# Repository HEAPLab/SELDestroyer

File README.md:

This README is a WIP.

# SEL Destroyer
This repository contains the hardware, firmware and software files of the
**SEL Destroyer** board, which is an electronic device to detect and destroy
the Single Event Latches (SELs) happening during SEE testing of electronic
components (radiation testing, laser-based testing, etc.).

The SEL destroyer can be also used as a normal voltage, current, or power monitoring device.

## Features
...

## Repository structure
- The `hardware` directory contains the KiCad files
  - See the hardware readme (WIP)
- The `firmware` directory contains the MPLAB X project (XC8 compiler) to program the PIC microcontroller
  - See the firmware readme (WIP)
- The `software` directory contains the host software (PC-side)
  - Check the software [README](software/README.md)

## License
MIT license, see the [LICENSE](LICENSE) file.

## Acknowledgments

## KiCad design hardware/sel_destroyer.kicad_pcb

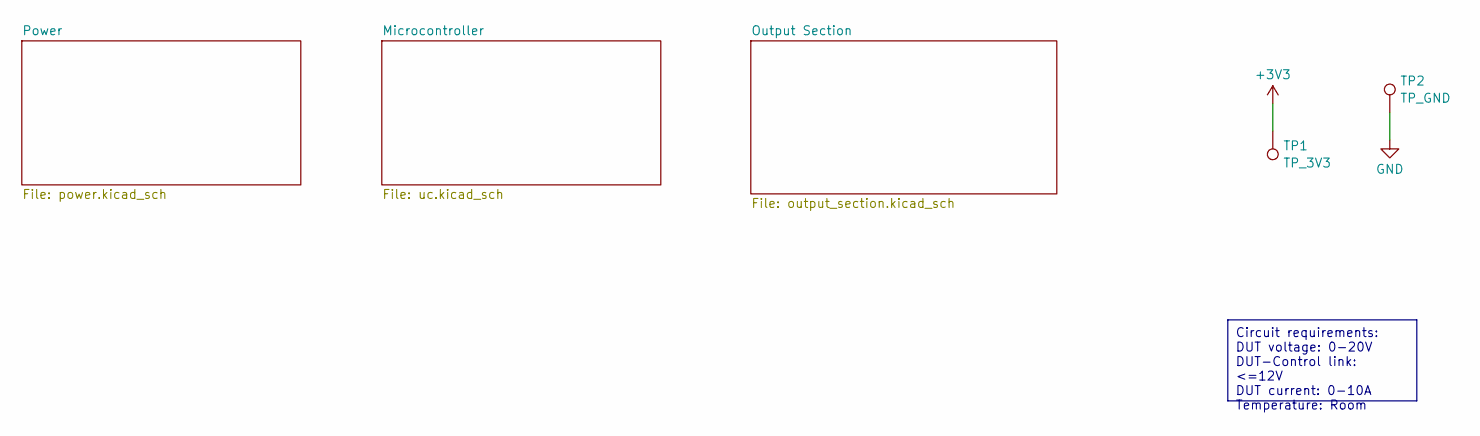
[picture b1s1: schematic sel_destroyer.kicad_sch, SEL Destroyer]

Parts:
TP1: TP_3V3; TestPoint_Loop_D1.80mm_Drill1.0mm_Beaded
TP2: TP_GND; TestPoint_Loop_D1.80mm_Drill1.0mm_Beaded

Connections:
+3V3: TP1.1; also elsewhere on the board
GND: TP2.1; also elsewhere on the board

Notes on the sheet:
Circuit requirements: DUT voltage: 0-20V DUT-Control link: <=12V DUT current: 0-10A Temperature: Room

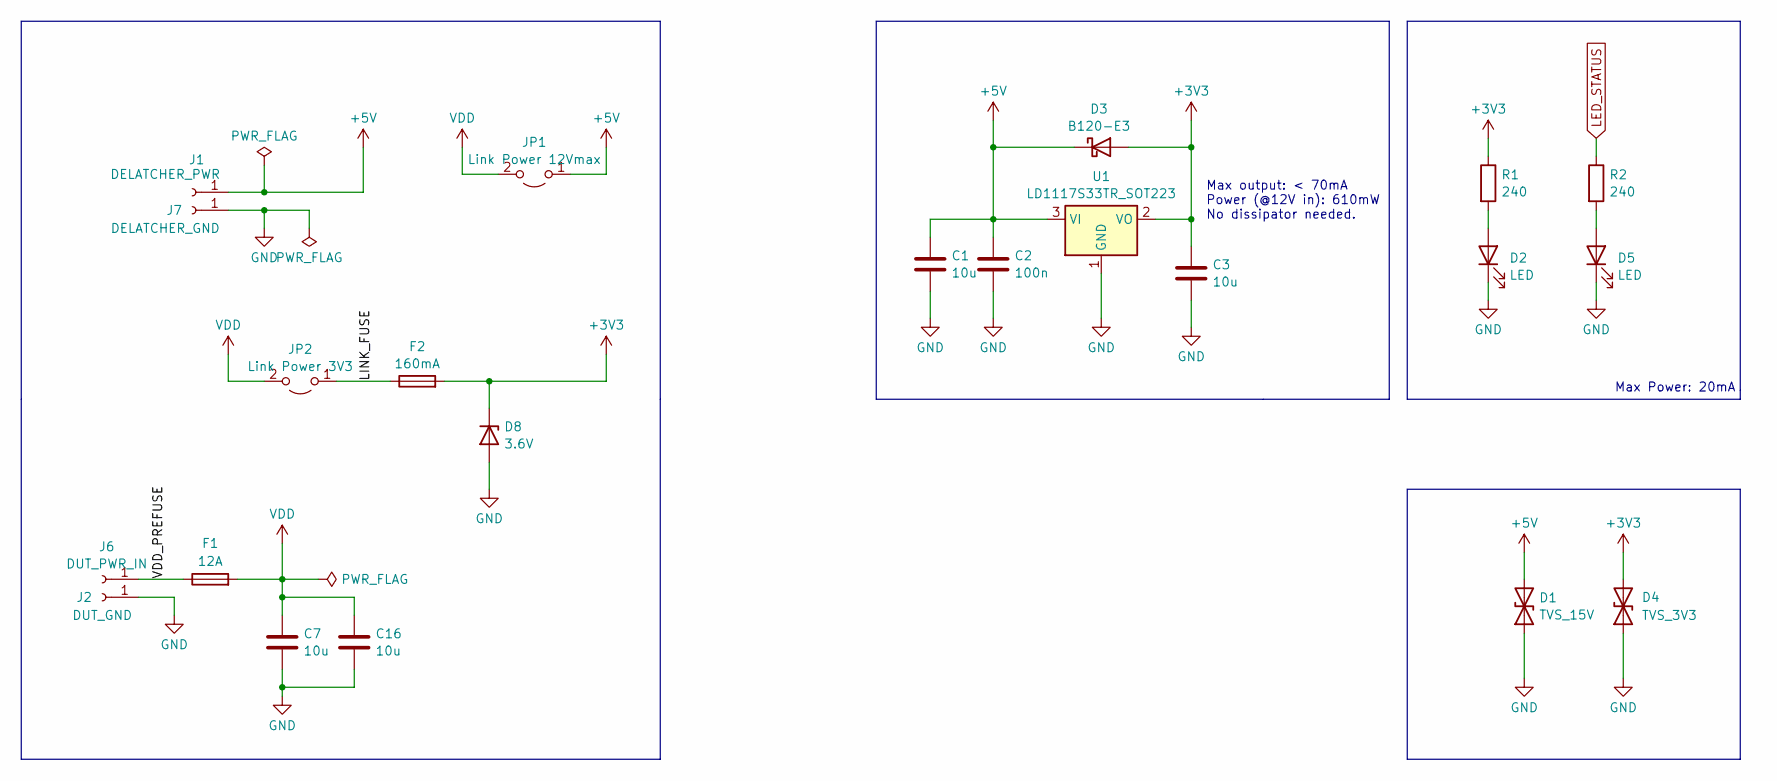
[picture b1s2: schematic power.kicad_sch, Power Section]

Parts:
C1, C3: 10u; C_0805_2012Metric_Pad1.18x1.45mm_HandSolder
C2: 100n; C_0805_2012Metric_Pad1.18x1.45mm_HandSolder
C7, C16: 10u; C_1206_3216Metric_Pad1.33x1.80mm_HandSolder
D1: TVS_15V; D_0603_1608Metric_Pad1.05x0.95mm_HandSolder
D2, D5: LED; LED_0805_2012Metric_Pad1.15x1.40mm_HandSolder
D3: B120-E3; D_SMA
D4: TVS_3V3; D_0603_1608Metric_Pad1.05x0.95mm_HandSolder
D8: 3.6V; D_SMB_Handsoldering
F1: 12A; Fuse_1206_3216Metric_Pad1.42x1.75mm_HandSolder
F2: 160mA; Fuse_1206_3216Metric_Pad1.42x1.75mm_HandSolder
J1: DELATCHER_PWR; CT3151
J2: DUT_GND; CT3151
J6: DUT_PWR_IN; CT3151
J7: DELATCHER_GND; CT3151
JP1: Link Power 12Vmax; PinHeader_1x02_P2.54mm_Vertical
JP2: Link Power 3V3; PinHeader_1x02_P2.54mm_Vertical
R1, R2: 240; R_0805_2012Metric_Pad1.20x1.40mm_HandSolder
U1: LD1117S33TR_SOT223; SOT-223-3_TabPin2

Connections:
+3V3: C3.1, D3.2 (A), D4.2 (A2), D8.1 (K), F2.2, R1.1, U1.2 (VO); also elsewhere on the board
+5V: C1.1, C2.1, D1.2 (A2), D3.1 (K), J1.1, JP1.1 (A), U1.3 (VI)
/Power/LINK_FUSE: F2.1, JP2.1 (A)
/Power/VDD_PREFUSE: F1.1, J6.1
GND: C1.2, C2.2, C3.2, C7.2, C16.2, D1.1 (A1), D2.1 (K), D4.1 (A1), D5.1 (K), D8.2 (A), J2.1, J7.1, U1.1 (GND); also elsewhere on the board
LED_STATUS: R2.1; also elsewhere on the board
unnamed: D2.2 (A), R1.2
unnamed: D5.2 (A), R2.2
VDD: C7.1, C16.1, F1.2, JP1.2 (B), JP2.2 (B); also elsewhere on the board

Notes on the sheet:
Max Power: 20mA
Max output: < 70mA Power (@12V in): 610mW No dissipator needed.

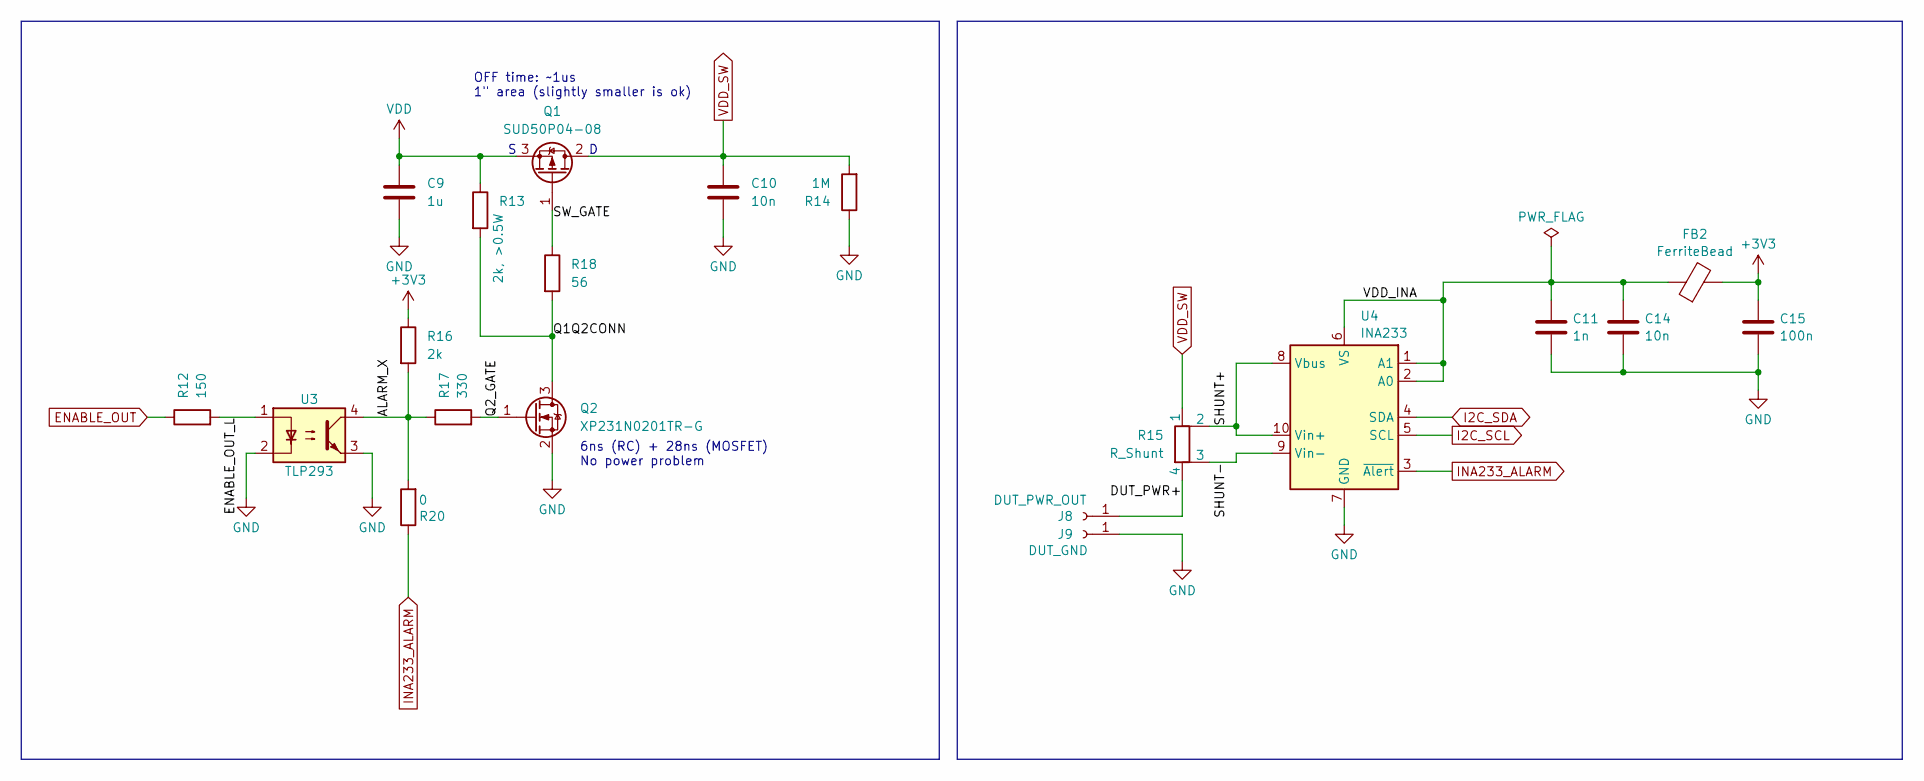
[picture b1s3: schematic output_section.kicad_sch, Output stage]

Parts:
C9: 1u; C_0805_2012Metric_Pad1.18x1.45mm_HandSolder
C10, C14: 10n; C_0805_2012Metric_Pad1.18x1.45mm_HandSolder
C11: 1n; C_0805_2012Metric_Pad1.18x1.45mm_HandSolder
C15: 100n; C_0805_2012Metric_Pad1.18x1.45mm_HandSolder
FB2: FerriteBead; L_0805_2012Metric_Pad1.15x1.40mm_HandSolder
J8: DUT_PWR_OUT; CT3151
J9: DUT_GND; CT3151
Q1: SUD50P04-08; TO-252-2
Q2: XP231N0201TR-G; SOT-23
R12: 150; R_0805_2012Metric_Pad1.20x1.40mm_HandSolder
R13: 2k, >0.5W; R_0805_2012Metric_Pad1.20x1.40mm_HandSolder
R14: 1M; R_0805_2012Metric_Pad1.20x1.40mm_HandSolder
R15: R_Shunt; R_Shunt_Vishay_WSK2512_6332Metric_T2.21mm
R16: 2k; R_0805_2012Metric_Pad1.20x1.40mm_HandSolder
R17: 330; R_0805_2012Metric_Pad1.20x1.40mm_HandSolder
R18: 56; R_0805_2012Metric_Pad1.20x1.40mm_HandSolder
R20: 0; R_0805_2012Metric_Pad1.20x1.40mm_HandSolder
U3: TLP293; SOIC-4_4.55x2.6mm_P1.27mm
U4: INA233; VSSOP-10_3x3mm_P0.5mm

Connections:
+3V3: C15.1, FB2.2, R16.1; also elsewhere on the board
/Output Section/DUT_PWR+: J8.1, R15.4
/Output Section/ENABLE_OUT_L: R12.2, U3.1
/Output Section/Q1Q2CONN: Q2.3 (D), R13.2, R18.2
/Output Section/Q2_GATE: Q2.1 (G), R17.2
/Output Section/SHUNT+: R15.2, U4.8 (Vbus), U4.10 (Vin+)
/Output Section/SHUNT-: R15.3, U4.9 (Vin-)
/Output Section/SW_GATE: Q1.1 (G), R18.1
/Output Section/VDD_INA: C11.1, C14.1, FB2.1, U4.1 (A1), U4.2 (A0), U4.6 (VS)
ENABLE_OUT: R12.1; also elsewhere on the board
GND: C9.2, C10.2, C11.2, C14.2, C15.2, J9.1, Q2.2 (S), R14.1, U3.2, U3.3, U4.7 (GND); also elsewhere on the board
I2C_SCL: U4.5 (SCL); also elsewhere on the board
I2C_SDA: U4.4 (SDA); also elsewhere on the board
INA233_ALARM: R20.1, U4.3 (~Alert); also elsewhere on the board
unnamed: R16.2, R17.1, R20.2, U3.4
VDD: C9.1, Q1.3 (S), R13.1; also elsewhere on the board
VDD_SW: C10.1, Q1.2 (D), R14.2, R15.1

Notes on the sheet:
OFF time: ~1us 1" area (slightly smaller is ok)
6ns (RC) + 28ns (MOSFET) No power problem

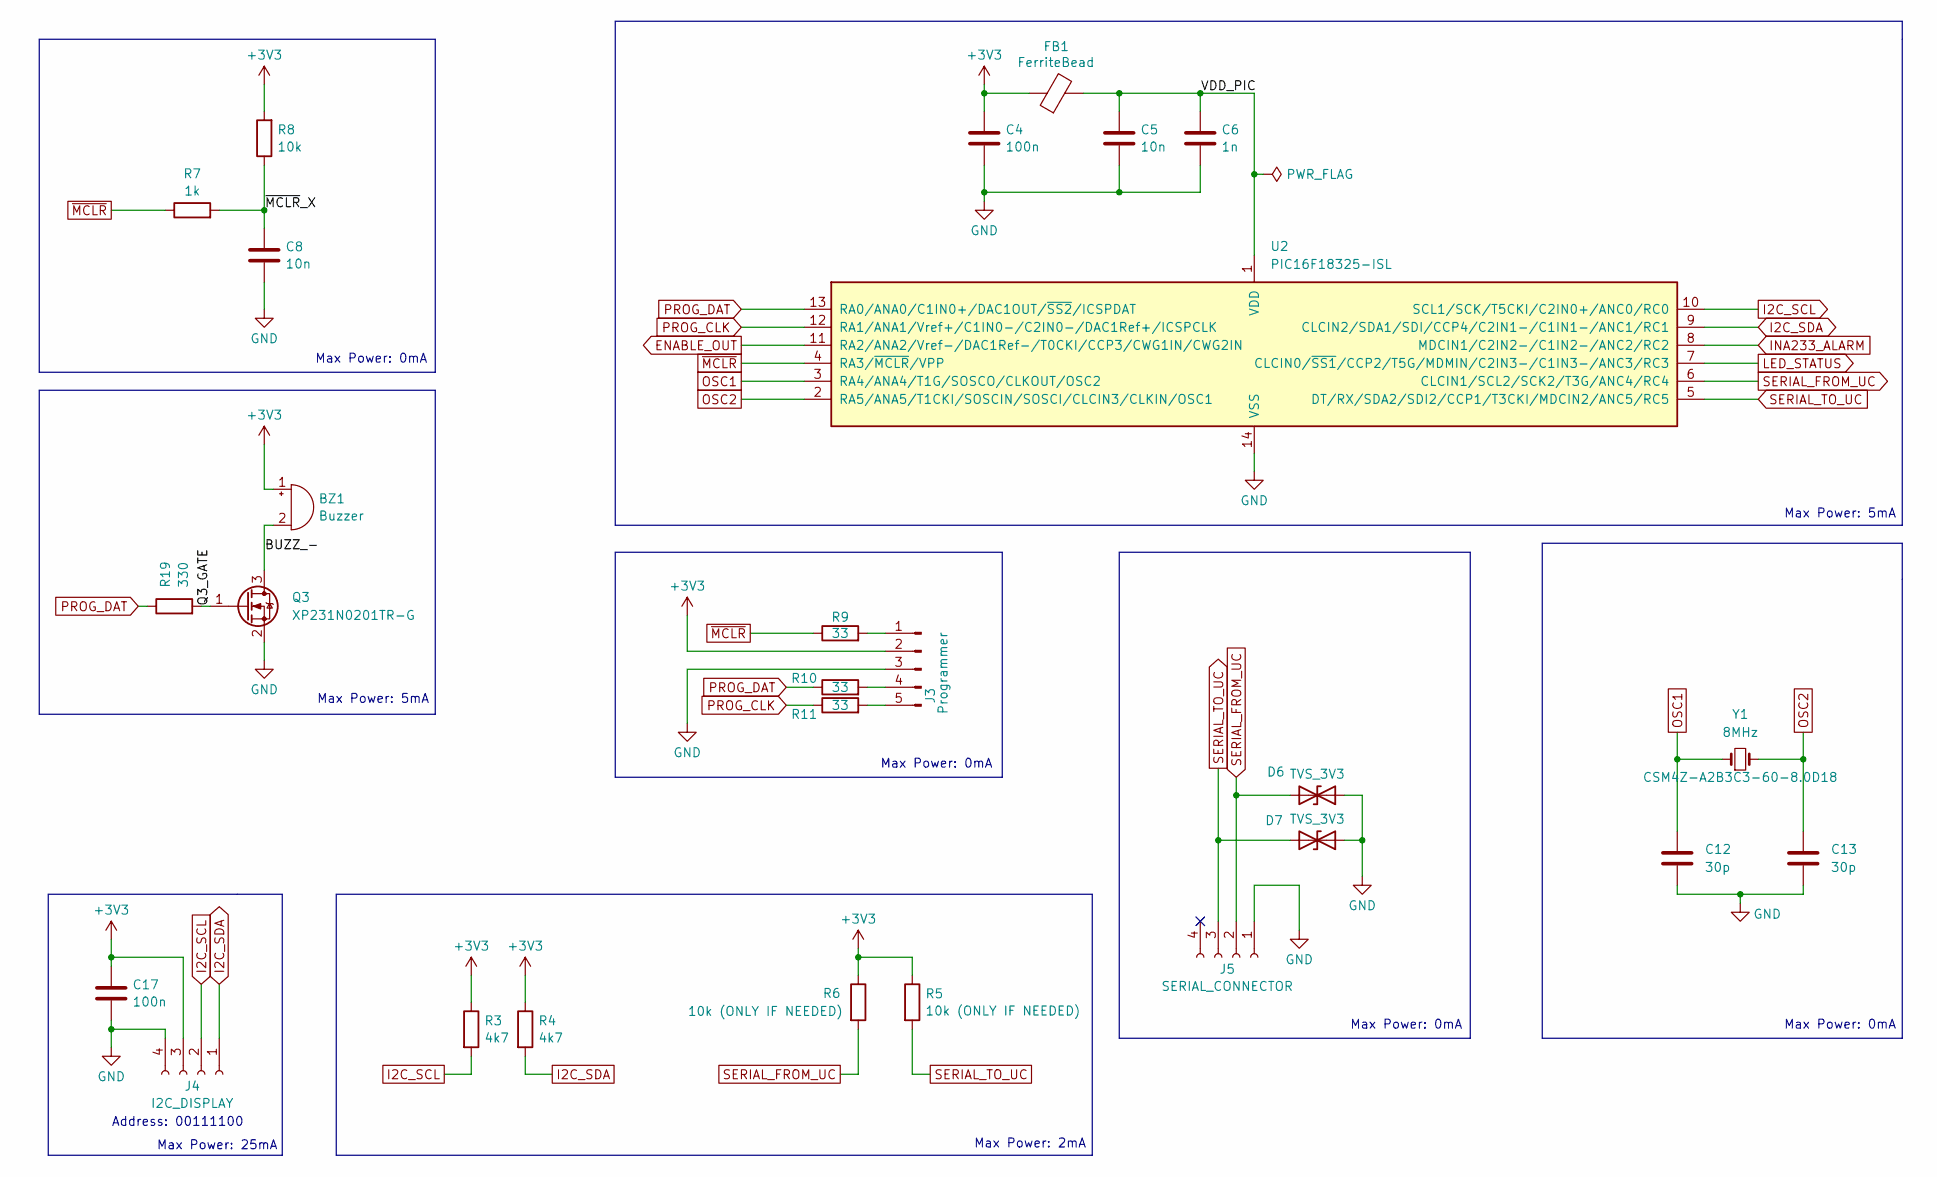
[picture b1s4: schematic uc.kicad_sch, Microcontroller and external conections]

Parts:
BZ1: Buzzer; Buzzer_CUI_CPT-9019S-SMT
C4, C17: 100n; C_0805_2012Metric_Pad1.18x1.45mm_HandSolder
C5, C8: 10n; C_0805_2012Metric_Pad1.18x1.45mm_HandSolder
C6: 1n; C_0805_2012Metric_Pad1.18x1.45mm_HandSolder
C12, C13: 30p; C_0805_2012Metric_Pad1.18x1.45mm_HandSolder
D6, D7: TVS_3V3; D_0603_1608Metric_Pad1.05x0.95mm_HandSolder
FB1: FerriteBead; L_0805_2012Metric_Pad1.15x1.40mm_HandSolder
J3: Programmer; PinHeader_1x05_P2.54mm_Vertical
J4: I2C_DISPLAY; PinSocket_1x04_P2.54mm_Vertical
J5: SERIAL_CONNECTOR; PinSocket_1x04_P2.54mm_Horizontal
Q3: XP231N0201TR-G; SOT-23
R3, R4: 4k7; R_0805_2012Metric_Pad1.20x1.40mm_HandSolder
R5, R6: 10k (ONLY IF NEEDED); R_0805_2012Metric_Pad1.20x1.40mm_HandSolder
R7: 1k; R_0805_2012Metric_Pad1.20x1.40mm_HandSolder
R8: 10k; R_0805_2012Metric_Pad1.20x1.40mm_HandSolder
R9, R10, R11: 33; R_0805_2012Metric_Pad1.20x1.40mm_HandSolder
R19: 330; R_0805_2012Metric_Pad1.20x1.40mm_HandSolder
U2: PIC16F18325-ISL; SOIC-14_3.9x8.7mm_P1.27mm
Y1: 8MHz; Crystal_SMD_HC49-SD

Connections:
+3V3: BZ1.1 (+), C4.1, C17.1, FB1.1, J3.2, J4.3, R3.1, R4.1, R5.1, R6.1, R8.2; also elsewhere on the board
/Microcontroller/BUZZ_-: BZ1.2 (-), Q3.3 (D)
/Microcontroller/Q3_GATE: Q3.1 (G), R19.2
/Microcontroller/VDD_PIC: C5.1, C6.1, FB1.2, U2.1 (VDD)
/Microcontroller/~MCLR_X: C8.1, R7.2, R8.1
ENABLE_OUT: U2.11 (RA2/ANA2/Vref-/DAC1Ref-/T0CKI/CCP3/CWG1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); also elsewhere on the board
GND: C4.2, C5.2, C6.2, C8.2, C12.2, C13.2, C17.2, D6.1 (A1), D7.1 (A1), J3.3, J4.4, J5.1, Q3.2 (S), U2.14 (VSS); also elsewhere on the board
I2C_SCL: J4.2, R3.2, U2.10 (SCL1/SCK/T5CKI/C2IN0+/ANC0/RC0); also elsewhere on the board
I2C_SDA: J4.1, R4.2, U2.9 (CLCIN2/SDA1/SDI/CCP4/C2IN1-/C1IN1-/ANC1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); also elsewhere on the board
INA233_ALARM: U2.8 (MDCIN1/C2IN2-/C1IN2-/ANC2/RC2); also elsewhere on the board
LED_STATUS: U2.7 (CLCIN0/~SS1/CCP2/T5G/MDMIN/C2IN3-/C1IN3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); also elsewhere on the board
unnamed: J3.1, R9.2
unnamed: J3.4, R10.2
unnamed: J3.5, R11.2
OSC1: C12.1, U2.3 (RA4/ANA4/T1G/SOSCO/CLKOUT/OSC2), Y1.1
OSC2: C13.1, U2.2 (RA5/ANA5/T1CKI/SOSCIN/SOSCI/CLCIN3/CLKI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), Y1.2
PROG_CLK: R11.1, U2.12 (RA1/ANA1/Vref+/C1IN0-/C2IN0-/DAC1Ref+/I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)
PROG_DAT: R10.1, R19.1, U2.13 (RA0/ANA0/C1IN0+/DAC1OUT/~SS2/ICSPDAT)
SERIAL_FROM_UC: D6.2 (A2), J5.2, R6.2, U2.6 (CLCIN1/SCL2/SCK2/T3G/ANC4/RC4)
SERIAL_TO_UC: D7.2 (A2), J5.3, R5.2, U2.5 (DT/RX/SDA2/SDI2/CCP1/T3CKI/MDCIN2/ANC5/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)
~MCLR: R7.1, R9.1, U2.4 (RA3/~MCLR/VPP)

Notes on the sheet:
Max Power: 2mA
Max Power: 0mA
Address: 00111100
Max Power: 5mA
Max Power: 25mA

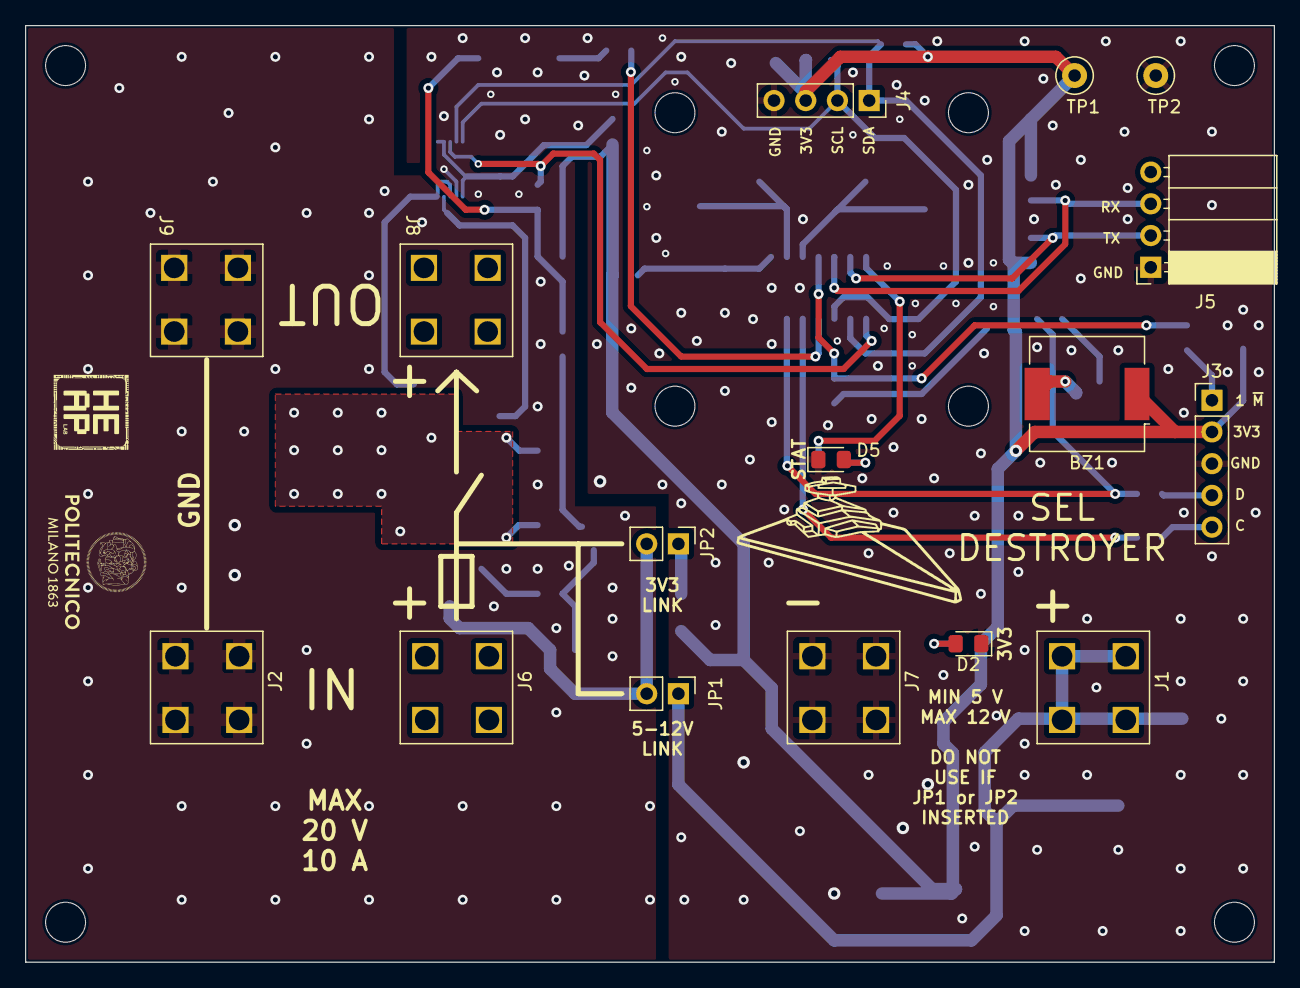
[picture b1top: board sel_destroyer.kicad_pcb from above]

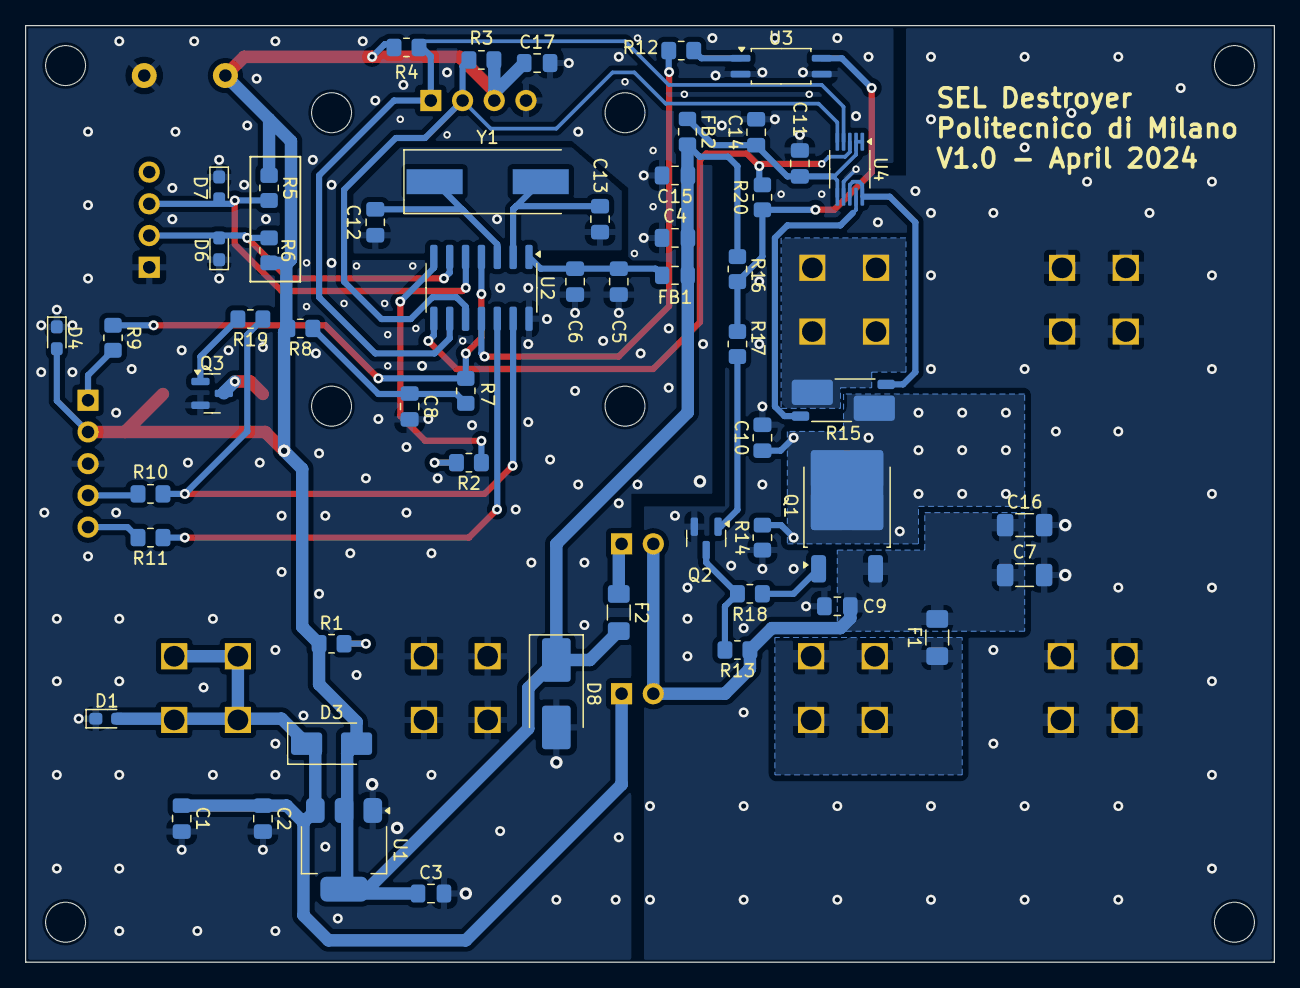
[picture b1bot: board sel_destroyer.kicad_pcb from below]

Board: 2 copper layers, 100.0 x 75.0 mm, 71 parts (55 on the bottom side), 37 nets.

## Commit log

2024-04-27 [Host] Initial structure
2024-04-27 [Host] Add vscode stuff in gitignore
2024-04-28 [Host] Implemented class flow down to serial port
2024-04-28 [Host] Setup for testing
2024-04-28 [Firmware] Import firmware from old repository
2024-04-28 [Host] Add connection parameters
2024-04-28 [Hardware] Import from old repository
2024-05-05 [Firmware] I2C implementation
2024-05-05 [Firmware] INA233 implementation
2024-05-05 [Firmware] First implementation of the display
2024-05-05 [Firmware] First working example of the display
2024-05-11 [Firmware] Add display management
2024-05-11 [Firmware] Working RX/TX serial with interrupts
2024-05-12 [Firmware] First working protocl
2024-05-12 [Firmware] Reading/Writing config to EEPROM
2024-05-20 [Host] Protocol update
2024-05-20 [Firmware] Various fixes (mainly overflow in the display visualization)
2024-05-20 [Firmware] INA233 OC limit set (first time working)
2024-05-20 [Firmware] Set external oscillator
2024-05-20 [Firmware] Minimal SEL detection implementation
2024-05-21 [Host] Reading V/I values
2024-05-21 [Firmware] Fix data size of some configuration items and messages
2024-05-21 [Firmware] Protocol to receive new configurations
2024-05-21 [Host] Documentation and debug flag
2024-05-21 [Host] Reading configuration methods
2024-05-21 [Firmware/Host] First working full flow (but slow reset SEL response)
2024-05-23 [Host] Split set output status from config
2024-05-23 [Host] [Lib] Fix closing procedure
2024-05-23 [Host] [Lib] Add version and fix ADC config bit composition
2024-05-23 [Host] [CLI] First implementation
2024-05-23 [Firmware] First working version
2024-05-23 [Firmware] Fix MFR send to device
2024-05-23 [Host] [CLI+Lib] Monitoring SEL events
2024-05-29 [Firmware] Enable watchdog
2024-05-29 [Firmware] Minor fixes around to improve reliability
2024-05-29 Preliminary README.md
2024-05-29 Create LICENSE
